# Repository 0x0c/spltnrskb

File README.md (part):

# nrsk 分割キーボード v2（基板と筐体）

KLE レイアウト（`kle/left.json`、`kle/right.json`）から生成した、左右分割・有線接続のキーボード基板です。
KiCad 10 のプロジェクト（回路図と配線済み基板）、製造用ガーバー、BOM、QMK ファームウェア設定を含みます。筐体のデータ（アクリルのレーザーカット用 DXF/SVG と 3D プリント用 STL）も入っています。

v2 では Pro Micro などのマイコンボードをやめ、RP2040 と QSPI Flash、USB-C コネクタなどを基板に直接実装しました。
マイコンボード用に設けていた内側の帯（約 20 mm）がなくなり、基板はキー領域とほぼ同じ大きさになっています。

| 項目 | 内容 |
| --- | --- |
| キー数 | 左 38 + 右 42 = 80 |
| マイコン | RP2040（QFN-56、12 MHz 水晶、I/O 3.3 V）と 16 MB の QSPI Flash W25Q128JV を左右に 1 組ずつ、裏面に直接実装 |
| USB | USB-C（USB 2.0）を左右それぞれに搭載 |
| 左右接続 | USB-C（片側にもう 1 つ、PC 用と同じレセプタクル）と USB-C ケーブル（C-C、データ通信用）。QMK の PIO シリアル（半二重、D+ の 1 本）と 5 V 給電 |
| スイッチ | Cherry MX 互換、Kailh MX ホットスワップソケット（裏面） |
| 基板 | 2 層、左 161.1 × 126.3 mm、右 180.5 × 126.3 mm（キー配列の外周から 3 mm を基本に、上端を 6 mm、内側を左 17.0 mm・右 12.6 mm 広げて OLED、USB-C 2 つ、マイコンの場所を確保）、四隅は半径 4 mm の角丸、M2 取付穴 × 8（片側あたり）、表裏とも GND のベタ（約 5 mm 間隔のビアで表裏をつなぐ） |
| 筐体 | 左 178.1 × 143.3 mm、右 197.5 × 143.3 mm、高さ 15.6 mm（3D プリント版）／ 16.5 mm（アクリル版）、いずれもプレート上面まで |
| 外観 | プレートは透明アクリル 1.5 mm、アクリル版の枠と底板はマットクリア 3 mm。プレートは外周の切り欠きなし。USB-C の 2 つの穴はコネクタの外形ぴったりで、高さも形も同じ（基板の舌でコネクタを壁の中まで出し、口は外面の約 1.3 mm 内側）。3D プリントのトレイは外周の角をフィレット加工（B のプレートも上面の外周に半径 1 mm の R） |
| 表示 | 0.91 インチ OLED（128×32）を左右に 1 枚ずつ、プレートと面一のハーフミラーアクリルのカバー付き。高さは増えない |
| ホイール | 左上と右上の角にサムホイール（ロータリーエンコーダー Alps EC05E1220401 で読み取り、1 回転 12 クリック）。高さは増えない |
| ドラム | 右半分の上段、F12 の右の空きに、手前と奥へ転がすドラム式ダイヤル（ロータリーエンコーダー Alps EC10E1220505 で読み取り、1 回転 24 クリック）。縦スクロールを送る。高さは増えない |
| 3D ビューア | http://www.0x0c.me/spltnrskb/ 、組み立てガイドは http://www.0x0c.me/spltnrskb/assembly.html 、写実的な 3D 表示は http://www.0x0c.me/spltnrskb/views.html 、エンコーダーの検証基板の 3D 表示は http://www.0x0c.me/spltnrskb/enctest-views.html （GitHub Pages、`main` への Push で自動更新） |

基板の表と裏です（KiCad の 3D 表示）。裏面は裏から見た向きなので、左右が反転して見えます。

| | 左 | 右 |
| --- | --- | --- |
| 表 |  |  |
| 裏 |  |  |

完成イメージ（Blender でレンダリング）です。筐体は 2 つの 3D プリント版を採用しています。左が A（3D プリントのトレイ + 透明アクリルのプレート）、右が B（プレートも 3D プリント）です。A はプレートを上から小ねじで、B は底からネジで留めます（B の上面にはネジが見えません）。

A と B は http://www.0x0c.me/spltnrskb/views.html で、3D のまま好きな角度から見られます。ドラッグで回転、ホイールかピンチで拡大します。「自動回転」をオンにすると、ゆっくり回り続けます（触っている間は止まり、手を離して 3 秒ほどで再開します）。形状、材質、照明は Blender のレンダリングと同じです。基板は、KiCad から書き出した実装済みのものです（`gen/export_3d.py` で `build/3d/` に作る）。「パストレース」をオンにすると、手を止めている間、ブラウザでパストレーシング（three-gpu-pathtracer）が進み、写真のような画が得られます。GPU を使い続けるので、最初はオフです。オンのときの自動回転は、選んだサンプル数まで描いてから 30° ずつ回ります。ボケとケーブル、台座（3°、6°、9°）も表示を切り替えられます。手元で開くときは `python3 -m http.server -d docs` で [docs/views.html](docs/views.html) を配信してください。ページの下には寄りの画像（打鍵する位置から、背面、側面、角、キーキャップ、ホイール、ドラム式ダイヤル、差込口。ケーブルを抜いた全体・背面・差込口も）が並び、クリックすると拡大します。台座に載せた姿も、側面と背面の 2 枚があります。3D 表示のモデル・照明・床の影は `gen/export_web3d.sh`（4 分ほど）で、寄りの画像は `gen/render_details.sh`（1 枚 3 分ほど）で作り直せます。

## 回路

各半分に同じ回路が載っています。Raspberry Pi の RP2040 設計ガイド（Hardware design with RP2040）の最小構成に、保護部品を加えた構成です。

| 機能 | 部品 |
| --- | --- |
| QSPI Flash | W25Q128JVS（16 MB、SOIC-8 208 mil）、0.1 µF |
| クロック | 12 MHz 水晶（3225）、15 pF × 2、XOUT に 1 kΩ 直列 |
| 電源 | VCC（5 V）→ LDO AP2112K-3.3（入出力 1 µF）→ 3V3。コアの 1.1 V は RP2040 内蔵レギュレータ（VREG_VIN／VREG_VOUT に 1 µF） |
| 電源のパスコン | IOVDD × 6、DVDD × 2、USB_VDD、ADC_AVDD にそれぞれ 0.1 µF、3V3 に 10 µF |
| USB | 27 Ω × 2（D+/D−）、CC 用 5.1 kΩ × 2（USB-C のデバイス認識用）、ESD 保護 USBLC6-2SC6 |
| 左右接続の USB-C | VBUS = VCC（5 V）、D+（A6、B6）= DATA、GND。D− と CC は未接続。DATA と VCC に ESD 保護 USBLC6-2SC6（PC 用の口と同じ部品） |
| 電源経路 | VBUS → ポリスイッチ 500 mA → ショットキーダイオード B5819W → VCC（5 V、左右接続の USB-C で反対側にも給電） |
| リセットと書き込み | RUN を 10 kΩ でプルアップしたリセットスイッチ（裏面）。BOOTSEL は QSPI_SS から 1 kΩ を通したはんだジャンパー |
| 左右判定 | GP0 を 10 kΩ で左は 3V3、右は GND に接続 |

- ショットキーダイオードは逆流を防ぎます。左右接続のケーブルで給電されている側でも、PC 用の USB-C の VBUS には電圧が出ないので、両方の USB を挿してもホスト側に電流が逆流しません。USB を挿していない側が自分をマスタだと誤判定することもありません。
- RP2040 はブートローダーを ROM に持っています。Flash が空のときは USB を挿すだけで `RPI-RP2` ドライブとして見え、UF2 ファイルをコピーすれば書き込めます。一度 QMK を書き込んだあとは、リセットスイッチを素早く 2 回押すと同じ書き込みモードに入ります。ISP 書き込み器は必要ありません。
- 左右接続の DATA は、通電したまま抜き差しするコネクタから RP2040 の GPIO へ直接つながります。そこで、コネクタのすぐ後ろに ESD 保護素子を置いています。直列抵抗は入れていません。QMK の半二重 PIO ドライバは、相手側が弱く High に駆動している線を Low に引く方式で、抵抗を入れると Low の電圧が上がるためです。
- OLED は 3.3 V で動かします。サムホイールとドラム式ダイヤルのエンコーダーは、A 相と B 相を RP2040 の内蔵プルアップで読み、共通端子を GND につないでいます。

### マルチプレクサは不要

片側のマトリックスは 6 行 × 8 列で、使う GPIO は 14 本です。
RP2040 の GPIO は 30 本あるので、シリアル通信 1 本、左右判定 1 本、I2C 2 本、エンコーダー 2 本を足しても十分に足ります。
列 7 を使うのは右の `\` キーだけで、左の列 7 は未接続です。QMK の分割キーボードは左右で同じ列数を前提とするため、左右とも 6 × 8 のマトリックスにそろえています。

### ピン割り当て（左右共通）

| 用途 | GPIO |
| --- | --- |
| ROW0〜ROW5 | GP4〜GP9 |
| COL0〜COL7 | GP10〜GP14、GP16〜GP18（GP15 は QFN の角で配線しにくいため使わない） |
| I2C1（OLED） | SDA = GP2、SCL = GP3 |
| サムホイールのエンコーダー | A 相 = GP19、B 相 = GP20（共通端子は GND） |
| ドラム式ダイヤルのエンコーダー（右だけ） | A 相 = GP22、B 相 = GP23（共通端子は GND） |
| 左右間データ | GP1、左右接続の USB-C の D+ |
| 左右判定 | GP0 |
| 予備 | GP15、GP21、GP24〜GP29（左は GP22、GP23 も） |

左右接続の USB-C は、VBUS に VCC（5 V）、D+ に DATA、GND をつなぎ、D− と CC は未接続です。D+ は表裏の 2 つのピン（A6、B6）をどちらも DATA につないでいるので、ケーブルはどちら向きに挿しても動きます。

- CC に抵抗（5.1 kΩ）を付けていないので、規格どおりの PC や充電器は、この口につながった相手を受電側と認識せず、VBUS に電圧を出しません。PC のケーブルを誤ってこの口に挿しても、何も起きません。
- 一方、この口の VBUS には、キーボードに電源が入っている間は VCC がそのまま出ています。キーボードを PC 用の口で PC につないだまま、この口を別の PC や充電器につながないでください。
- データ線のない充電専用のケーブルでは、左右が通信しません。データ通信に対応した USB 2.0 以上の C-C ケーブルを使ってください。

## 配置

- 表面: スイッチ、OLED、右半分のドラム式ダイヤルのエンコーダーです。スイッチプレートより上に出るのは、ドラム式ダイヤルの部品だけです（ベゼルで覆います）。
- 裏面: ホットスワップソケット、ダイオード、RP2040、Flash、LDO などの周辺部品、リセットスイッチ、BOOTSEL パッド、USB-C × 2、サムホイールのエンコーダー。
- 部品実装を頼む電子部品は、すべて裏面に載せています。JLCPCB の部品実装が片面で済み、両面より安くなります。部品の配置も、キーキャップや OLED のカバーを避ける制約がなくなり、単純になります。
- 2 つの USB-C はどちらも奥の辺（上端）に置き、ケーブルを後ろへ出します。左右接続用は内側の角寄り（OLED の上）、PC 用はその 18 mm 外側です。同じ部品なので、2 つの差込口の高さはそろいます。どちらも基板の外形を幅 12 mm の舌として壁の中まで伸ばし、舌の先端へコネクタを載せています。コネクタの口は舌の先端とそろえてあり、ケースの外面から約 1.3 mm 内側です（厚さ 0.8 mm の壁と、0.5 mm のすき間）。舌の先端の角は半径 2.5 mm、付け根は半径 0.8 mm の R を付けてあり、基板単体で持っても角が手に刺さりません。付け根の R は、筐体の壁とトンネルの角を避ける大きさです。
- 基板と筐体は、左右それぞれのキー配列にぴったり合わせた大きさです（左は OLED の分だけ内側を広げています）。
- 2 u 以上のキー（左 Shift 2.25 u、右 Backspace 2 u、右 Enter 2.25 u）には PCB マウント型スタビライザの穴があります。
- 配線幅は信号線 0.2 mm、電源線（GND、VCC）0.4 mm、USB の 5 V 入力（VBUS からヒューズ、ダイオードまで）0.3 mm です。クリアランスは 0.15 mm（GND のベタは 0.3 mm）、ビアは 0.6/0.3 mm です。最小配線幅は 0.15 mm で、RP2040 や USB-C の細いピンに入る短い区間だけで使っています。JLCPCB などの標準仕様（最小 0.127 mm）で製造できます。
- RP2040 の電源ピンのパスコンは、ほかの部品より先に、電源側のパッドをピンへ向けて置いています（ピンからパスコンのパッドまで、左 4.3〜5.1 mm、右 4.3〜6.8 mm）。GND のベタをつなぐビアは、半田付けするパッドとその周り 0.3 mm には打ちません（ビアの穴に半田が吸われるのを防ぐため）。
- 裏面のシルクには、基板名のほかに `RESET`（リセットスイッチ）と `BOOT`（BOOTSEL パッド）の表示があります。`JLCJLCJLCJLC` の文字は、JLCPCB が製造番号を入れる位置の指定です。
- ホットスワップソケットのパッドには、ペースト層を出していません。ソケットは実装のあとに手で半田付けします。先に半田が盛られていると、ソケットが浮くためです。
- マイコン周りの部品番号はシルクに収まらないため、Fab 層に入れています。半田付けには `fab/<side>/nrsk-<side>-assembly-back.pdf`（裏面の実装図、左右反転済み）を使ってください。配線の確認には `fab/<side>/nrsk-<side>-copper.pdf` を使えます（1 ページ目が表面 F.Cu、2 ページ目が裏面 B.Cu で、どちらも外形付き）。

## サムホイール（角のダイヤル）

左半分の左上、右半分の右上の角に、親指でなぞって回すサムホイールを付けています。

- 形: 直径 29.2 mm、厚さ 4.1 mm のホイールで、外周に 32 山の丸い歯（深さ 0.5 mm）があります。歯は指のすべり止めです。角の丸みと同心に置いていて、縁が角から約 3.5 mm、両側面から約 1 mm 出ます。
- 位置: 基板と底のすき間（7 mm）に水平に寝かせています。壁の下側だけを切り欠くので、プレートと壁の上部は切れ目がありません。キーボードの高さも変わりません。
- 検出: 基板裏面のホイールの中心の真上に、中空シャフトのロータリーエンコーダー Alps EC05E1220401 を下向きに付けています。ホイール上面の六角ピン（対辺 1.66 mm）が、エンコーダーの六角穴（対辺 1.72 mm）に 2 mm 入って回転部を回します。エンコーダーの下面に当たらないよう、ホイール上面の中心（半径 6 mm）を 0.4 mm 下げています。基板には、回転部の下に 3 mm 角の穴があります。
- クリック: エンコーダーが内蔵するクリックを使い、1 回転 12 クリック（30° ごと）です。1 クリックで A 相と B 相がちょうど 1 周期進むので、クリックとファームウェアの 1 ステップは部品の中で一致しています。
- 軸: 3D プリント版はトレイの床から立てた軸（直径 3.6 mm）、アクリル版は底板の下から通す M3 ネジを軸にします。ホイールの下面には軸穴（直径 4 mm × 深さ 2 mm）があります。親指で押す横向きの力はこの軸で受け、エンコーダーには回転だけを伝えます。軸と軸穴の間に半径方向で 0.2 mm 以上のすき間を設けて、基板とケースの位置ずれでホイールがこじれないようにしています。
- 組み立て: 3D プリント版で基板をトンネルへ滑り込ませるとき、エンコーダーの下面は六角ピンの先端の約 0.3 mm 上を通ります。ホイールのある角を少し持ち上げて滑らせてください。基板を下ろすときは、ホイールの縁を指で少し回すと、ピンがエンコーダーの穴に入ります。
- 左の Esc キー: エンコーダーと Esc のホットスワップソケットが重ならないよう、基板の上端を 1 mm 余分に延ばしてホイールを上へずらしています。そのため、すべてのスイッチを同じ向きで取り付けます。
- ファームウェア: QMK のエンコーダー機能で読みます。エンコーダーは基板の裏で下を向いているので、A 相と B 相のピンを入れ替えて設定し、上から見た時計回りを正の向きとして扱います。USB をつないでいない側のホイールも、QMK が左右間の通信で送ります。

| | 左ホイール | 右ホイール |
| --- | --- | --- |
| 回す（レイヤー 0） | 音量 | ページ上下 |
| 回す（レイヤー 1） | 画面の明るさ | カーソル左右 |

割り当ては `keymap.c` の `encoder_update_user()` で変更できます。

検討段階の記録として、側面ダイヤルの 2 タイプ（サムホイール型と横向きノブ型）を比べたレンダリングは [docs/img/dial-study/dial-grid.jpg](docs/img/dial-study/dial-grid.jpg) にあります。サムホイール型を採用し、角に置きました。

読み取りの方式は、当初の磁気角度センサー AS5600 と磁石、ボールプランジャーの組み合わせから、市販のロータリーエンコーダーに変えました。理由と検討した代替案は [docs/specs/thumbwheel-encoder.md](docs/specs/thumbwheel-encoder.md) に、両者の断面の比較は [docs/img/encoder-study/sheet.jpg](docs/img/encoder-study/sheet.jpg) にあります。

## ドラム式ダイヤル（右上）

右半分の上段で、F12 の右に空いている 2 u の場所に、手前と奥へ転がすドラム式のダイヤルを付けています。奥へ転がすと上へ、手前へ転がすと下へスクロールします（レイヤー 1 では左右へスクロール）。

- 形: 直径 13 mm、幅 21.6 mm のドラムで、表面に斜めのローレット（ねじれ角 30°、溝 36 本、深さ 0.4 mm）があります。細かいローレットを出すため、光造形の樹脂で作ります（`case/print/right-drum.stl`）。
- 高さ: 軸は基板の上面から 7 mm です。ドラムの上端はプレートから 8.5 mm 出て、キーキャップの上面より 4.5 mm 低くなります。キーボードの高さは変わりません。
- 位置: ドラムを囲むベゼルは、左右のフードが同じ大きさの対称な形で、2 u の空きをほぼ埋めています。左は F12 との間のプレートの帯、右は筐体の壁で端が決まるので、ベゼルとドラムの中心は下の段の Backspace（2 u）の中心より約 0.7 mm 右に来ます。
- 検出: 軸が基板と平行な横型のロータリーエンコーダー Alps EC10E1220505（1 回転 24 クリック、12 パルス）を、ドラムの左に表面から差し込みます。ドラムの左端の六角ピン（対辺 1.66 mm）が、エンコーダーの六角穴（対辺 1.73 mm）に 1.6 mm 入って回します。ピンは根元から先まで対辺 1.66 mm の六角のままで、先端の縁だけを 0.2 mm 面取りしています。
- 軸受け: ドラムの右端の丸ピン（直径 2 mm）を、基板の穴 2 つに差し込んだ 3D プリントの軸受けブロックが受けます。ブロックの位置決めピンは基板の下へ出ないので、基板の下のサムホイールとは当たりません。ブロックの溝は上が開いた U 字で、入口を 1.8 mm に絞ってあるので、ピンを上から押し込むとはまって抜けません。指で押し下げる力は、エンコーダーとブロックの両方で受けます。
- ベゼル: 3D プリントのベゼル（`case/print/right-drum-bezel.stl`）の枠を、プレートの穴に収めます。枠の上面はプレートと面一で、段差はありません。プレートを載せる前にベゼルを基板の上に置き、上からプレートをかぶせます。枠の下のつばがプレートの下面に当たってベゼルが抜けるのを止め、軸受けブロックの上面とエンコーダー側の脚が下から支えます。ベゼルのフードがエンコーダーを覆い、もう一方のフードの天井が軸受けブロックを押さえます。A、B、アクリル版で同じ部品を使います。
- ファームウェア: QMK のエンコーダー機能で読みます（右半分の 2 個目のエンコーダー）。1 クリックで A 相と B 相が半周期だけ進むので、分解能（`resolution`）を 2 にしています。マウスのホイールのキーコードを送るため、QMK のマウスキー機能を有効にしています。実機で向きが逆なら、`gen/make_qmk.py` の `pin_a` と `pin_b` を入れ替えます。

設計の経緯と、検討した代替案は [docs/specs/drum-dial.md](docs/specs/drum-dial.md) にあります。

## OLED

左右に 0.91 インチの OLED モジュール（128×32、SSD1306、I2C）を 1 枚ずつ付けています。

- 配線: RP2040 の GP3（SCL）と GP2（SDA）に接続し、4.7 kΩ でプルアップしています。モジュールのピン順は GND / VCC / SCL / SDA です。VCC と GND が逆のモジュールもあるので、購入前に確認してください。
- 配置: 左右とも内側の端、1〜2 段目の高さに縦向きで置き、上端からの位置をそろえています。モジュールは左右とも同じ向き（ピンヘッダが下）なので、ファームウェアの表示の向きは 1 つで済みます。右は 3 段目のキーの上の切り欠きに収まり、左は基板の内側を広げて、カバーの周りに 5.5 mm の帯を取っています（次の「筐体」）。
- 取り付け: ピンヘッダの黒い樹脂スペーサーを外し、OLED のガラス上面が基板の上面から 2.5 mm の高さになるように、モジュールを基板に近づけて半田付けします。
- 筐体: ハーフミラーのアクリルのカバー（`case/laser/<side>-oled-cover`）を、プレートの切り欠きにはめ込みます。カバーの周りに残るプレートの帯は、筐体の外周（上辺と内側の辺）までも、横のキーキャップまでも 5.5 mm です。カバーの 4 つの角はすべて R7 です。筐体の角に面する角は筐体の角（R12.5）と同心なので、帯の幅は角でも変わりません。帯の近くの外周のネジは省いています。カバーの下端は OLED モジュールの端から 1.5 mm 下で、OLED の表示（ガラス）がカバーの中央に来るように置いています。そのため、右のカバーの下の Y キーとの帯だけは 2.7 mm です。ハーフミラーのアクリルは 2 mm 厚からしか市販されていません。そこで 3D プリント版は壁の上面をカバーの下だけ 0.5 mm 下げて、上面をプレートと面一にしています（アクリル版は 0.5 mm 高くなります）。カバーは OLED のガラス面と壁の上面に透明両面テープで貼り、ネジは使いません。消灯中は鏡のように見え、点灯すると表示が透けて見えます。カバーの周りに余白を取るため、基板の上端を 5 mm 延ばし（ホイールのためにさらに 1 mm 延ばして計 6 mm）、内側を広げています。
- 表示: QMK の `oled_task_user` で、USB をつないだ側にレイヤーと Caps Lock、もう一方に WPM を表示します。処理は `firmware/qmk/keyboards/nrsk/keymaps/default/keymap.c` にあります。

### OLED の高さ・角度の比較

検討段階の記録です（採用したのは、上に書いたプレートと面一のハーフミラーのカバーです）。画像は今の基板・筐体の形で描き直しています。台座の位置は外形から計算し、壁の上に収まるように置いています。
キーキャップに隠れにくい OLED の付け方を、高さ 0〜13 mm の 4 案（A〜D）と傾斜 2 案（E・F）で比べました。
座った目線と寄りのレンダリングを、取り付け方式ごとに [docs/img/render-grid.jpg](docs/img/render-grid.jpg) にまとめています。
台座の形状は `gen/oled_variants.py`、レンダリングは `gen/render_all.sh` で作り直せます。デフォルトは確認用のプレビュー（長辺 1200 px、数分）で、`FINAL=1 ./gen/render_all.sh` とすると高画質（長辺 2400 px）で出力します。
B〜F は OLED を基板の外側（壁の上）へ移すため、基板のコネクタから配線でつなぐ前提です。

## 筐体

3D プリントとアクリルのレーザーカットのどちらでも作れるよう、同じ寸法のサンドイッチ構造にしています。3D プリントのトレイを使う版は 2 種類あり、どちらも正式な仕様です。

- **A：トレイ + 透明アクリルのプレート** — トレイは 3D プリント、スイッチプレートは透明アクリル 1.5 mm（`case/laser/<side>-plate`）。プレート越しに基板が見えます。
- **B：全部 3D プリント** — プレートも 3D プリント（`case/print/<side>-plate.stl`）。スイッチの爪が掛かる周りだけ 1.5 mm で、ほかは裏に 2 mm の補強があり、上下を逆にして印刷します。中は見えません。
- **アクリル版** — 底板・枠・プレートをすべてアクリルのレーザーカットで積み重ねます。

トレイは A と B で共通です。壁の中を縦にネジ穴が通り、上面には丸いくぼみ、底には座ぐり（φ4.6 × 1.6 mm）があります。A は透明アクリルのプレートを、上から通したなべ小ねじ M2 × 16 mm と、底の座ぐりに押し込んだ M2 ナットで留めます。くぼみの下には六角のナット受けもありますが、使いません。ナット受けは上に開いているので、上から締めるネジではナットが引き上げられるだけで、プレートを締め付けられないためです。B は、プレート裏のボスに入れたヒートセットインサートへ、トレイの底の座ぐりから M2 × 12 mm のなべネジで留めるので、上面にネジは見えません。アクリル版は上から M2 × 20 mm で底板の下のナットまで共締めします。
基板は 8 か所の取り付け穴で筐体の底に固定し、スイッチプレートは外周のネジで留めます。
寸法の基準は MX の規格（プレート上面から基板上面まで 5.0 mm）です。

| 部分 | A / B（3D プリントのトレイ、`case/print/`） | アクリル版（`case/laser/`） |
| --- | --- | --- |
| 底 | トレイの床 2 mm、外周の下端 R2・上端 R0.6 のフィレット | 底板 3 mm（`<side>-bottom`） |
| 壁 | トレイと一体、幅 8 mm、高さ 14.1 mm。ホイールの上は外せる角キャップ（`<side>-wheel-cap.stl`）。キャップの下段から出た 2 つの爪（奥の壁と側面の壁に 1 つずつ）がトレイの溝に入るので、キャップは回りません | 枠 3 mm × 4 枚（差込口のある枠には切り欠き、`frame4` は切り欠きなし） |
| 基板の支持 | 床から高さ 7 mm のボス（φ4.6、下穴 φ1.6）に M2 × 6 mm タッピングネジ | M2 × 7 mm スペーサーに、上から M2 × 4 mm、下から M2 × 5 mm のネジ |
| プレート | A：透明アクリル 1.5 mm、上から M2 × 16 mm のなべ小ねじで底の座ぐりのナットへ／B：3D プリント（補強付き、裏のボスに M2 インサート）、底の座ぐりから M2 × 12 mm | 透明アクリル 1.5 mm、上から M2 × 20 mm とナットで底板まで共締め |
| ネジ本数 | 外周 左右 10 ずつ、基板 左右 8 ずつ | 同じ |

設計上の注意点です。

- 取り付け穴は、スペーサーやボスが裏面のパッドや配線に触れない位置へ置きました（穴の中心から銅箔まで 2.75 mm 以上）。穴の周りには配線禁止の領域を設けています。
- 2 つの USB-C は、基板の舌に載せて壁の中まで出しています。壁の外面にはコネクタの外形に 0.2 mm を足した角丸の長穴だけが開き、プラグの根元はすべてケースの外に出るので、ほとんどのケーブルが使えます。アクリル版は、舌とコネクタの高さの枠 2 枚（`frame2`、`frame3`）を、2 つの差込口をまたぐ 1 つの切り欠きで開けています。アクリルでは差込口の前に 0.8 mm の壁を残せず、差込口ごとに切ると間に固定できない小片が残るためです。プレートと最上段の枠は切れ目のない輪のままです。

- 3D プリント版のトレイは、差込口のまわりも分割しない一体の部品です。舌とコネクタは、奥の壁の中の上が閉じたトンネルに収まります。トンネルの高さは、舌の上に 2.3 mm の余裕があります。この余裕の分だけ基板を浮かせれば、裏面の部品がボスの上を通り抜けられます（実装済みの基板の 3D モデルで確かめた最小値は 1.5 mm）。トンネルの上には厚さ 1.2 mm の天井が残ります（OLED カバーの下のくぼみに掛かる、左右接続用の USB-C 側の一部は 0.7 mm）。
- 基板は、手前の縁を約 2° 持ち上げて手前の壁の上端を越えさせ、ボスより 2 mm 浮かせて奥の壁に近づけます。舌を 2 つのトンネルに差し込みながら奥へ 8 mm 滑らせ、手前を下ろしてボスに載せます。下の図は、左の USB-C の中心を通る断面で、左側がケース全体、右側が差込口まわりの拡大です。

- 基板を床から 7 mm 浮かせているのは、ホイールとエンコーダー、裏面の部品のためです。
- 底面には、リセットスイッチをピンで押すための φ3 mm の穴があります。
- トレイの幅は左 178.1 mm、右 197.5 mm です。どちらも 220 mm 角の造形範囲（Ender-3、Bambu Lab A1/P1/X1、Prusa MK4 など）に入ります。180 mm 角の機種（A1 mini など）では入りません。
- B のプレートは PETG など粘りのある材料が向いています。A のプレートと同じ DXF から、アクリルのほか FR4 1.6 mm やアルミ 1.5 mm で外注できます。
- アクリル版の枠 4 枚の合計は 12.0 mm です。設計上の理想値 12.1 mm より 0.1 mm 薄く、その分プレートがスイッチを押し下げますが、アクリル板自体の厚み公差（±0.2 mm 程度）の範囲内です。気になる場合は、スペーサーの下に薄いワッシャーを挟んでください。
- レーザーカット用のプレート（`case/laser/<side>-plate`）は、スイッチ穴の角に半径 0.3 mm の R を付けています。スタビライザーの穴とスイッチ穴の間の桟（幅 1.4 mm）はなくして、1 つの穴にしています。細い桟は切り出せず、鋭い角はアクリルの割れの起点になるためです。`make_case.py` は、切り出す部品に幅 1 mm 未満の部分がないことを確かめます。離れた部品がどれも 2 本以上のネジで留まることも確かめ、幅 3 mm 未満の箇所を一覧で表示します。
- レーザーカットを外注するときは、DXF（単位 mm、全線カット）をそのまま入稿できます。スイッチ穴 14.0 mm はカット幅の補正が前提なので、補正の有無を業者に確認してください。

`case/preview/viewer.html` は組み立て状態を回して見られる 3D ビューアです。http://www.0x0c.me/spltnrskb/ で公開しています（`.github/workflows/pages.yml`）。
基板は KiCad の 3D プレビューと同じ部品実装済みの姿で表示します（`gen/export_3d.py` で KiCad から書き出し、`gen/glb_mesh.py` でブラウザ向けに軽量化）。
「分解表示」をオンにすると、スライダーでレイヤーどうしの間隔を 0〜40 mm で変えられます。
「台座」で角度（なし、3°、6°、9°）を選ぶと、台座に載せて傾けた姿になります。ケース、プレート、基板、スイッチ、ダイヤル、ゴム足、台座は、チェックボックスでそれぞれ表示と非表示を切り替えられます。

組み立て手順は、同じデータを使ったインタラクティブな組み立てガイド（`case/preview/assembly.html`、公開版は [http://www.0x0c.me/spltnrskb/assembly.html](http://www.0x0c.me/spltnrskb/assembly.html)）で確認できます。手順ごとに部品が所定の位置に入るアニメーションと説明が出て、A・B・アクリル版と左右を切り替えられます。

### Fusion の設計と、基板を変えたときの更新

3D プリントの部品の形は、Autodesk Fusion の設計 `nrsk-left-case` と `nrsk-right-case`（Hybrid Design）が正です。対象はトレイ、B のプレート、ホイール、ホイールのキャップ、台座、ドラム式ダイヤル一式です。形を変えるときは、Fusion の GUI で編集します。リポジトリには、節目ごとに書き出した設計（`case/fusion/nrsk-<side>-case.f3d`）と部品ごとの STL（`case/fusion/<side>/`）を置いています。`gen/make_case.py` はその STL を読み込み、干渉チェックをしてから `case/print/` と `case/preview/` へ書き出します。アクリル版と、検証基板のトレイとプレートは、従来どおり `make_case.py` が作ります。

寸法の定数の正は `make_case.py` です。Fusion のユーザーパラメータは同じ名前で、同期のたびに `make_case.py` の値で上書きされます。Fusion で値を変えて決めたら、`make_case.py` にも書き戻してください。

Fusion のスクリプトは `fusion/` にあります。`fusion/link.sh` を 1 度実行すると、Fusion の「ユーティリティ」タブの「アドイン」から開く「スクリプトとアドイン」の一覧に載ります。

- `NrskCaseSync`：基板から来る寸法を Fusion の設計に反映します。
- `NrskCaseExport`：部品ごとの STL と `.f3d` を `case/fusion/` に書き出します。
- `NrskCaseLayout`：Fusion の画面で、各部品を組み立てた位置に表示します（台座は 3° だけ）。部品は書き出す座標系で作ってあるので、そのままではホイールが床に、プレートがトレイにめり込んで見えます。配置を動かすだけなので、書き出す STL は変わりません。
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
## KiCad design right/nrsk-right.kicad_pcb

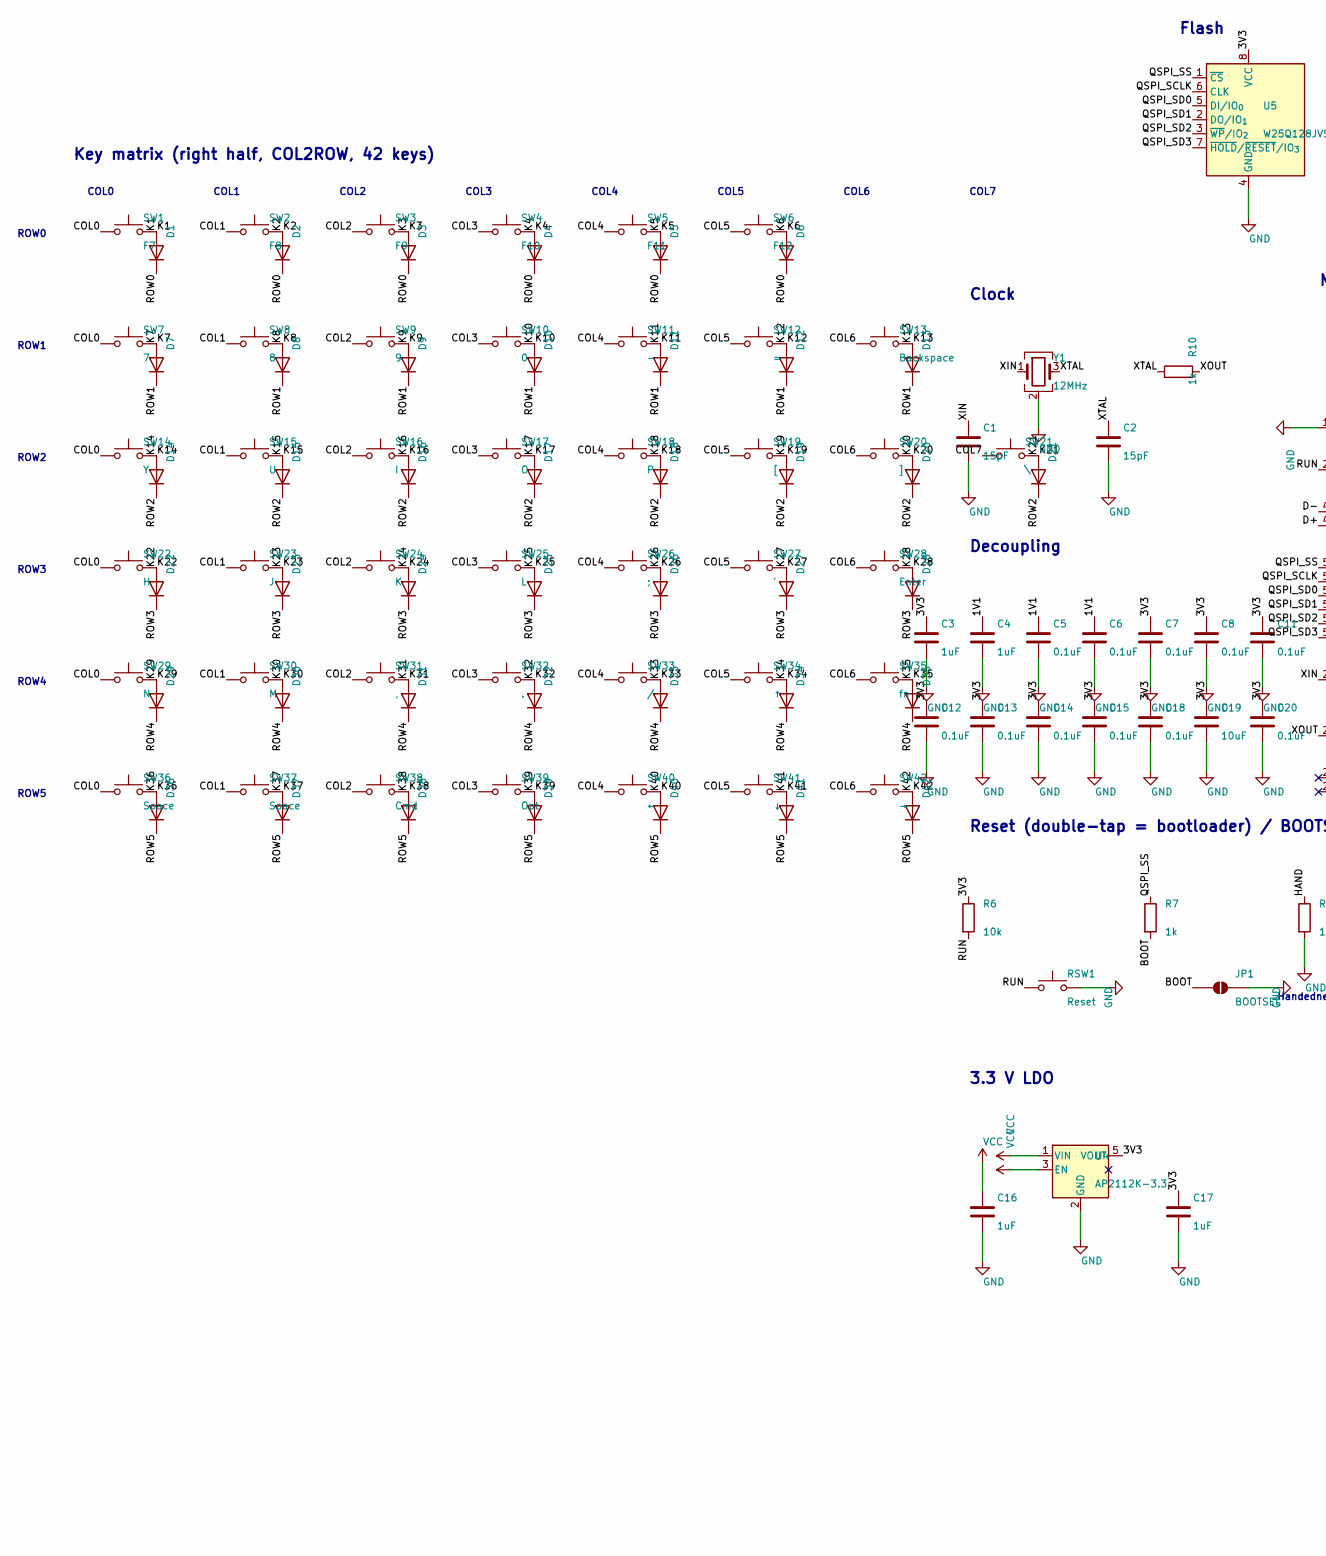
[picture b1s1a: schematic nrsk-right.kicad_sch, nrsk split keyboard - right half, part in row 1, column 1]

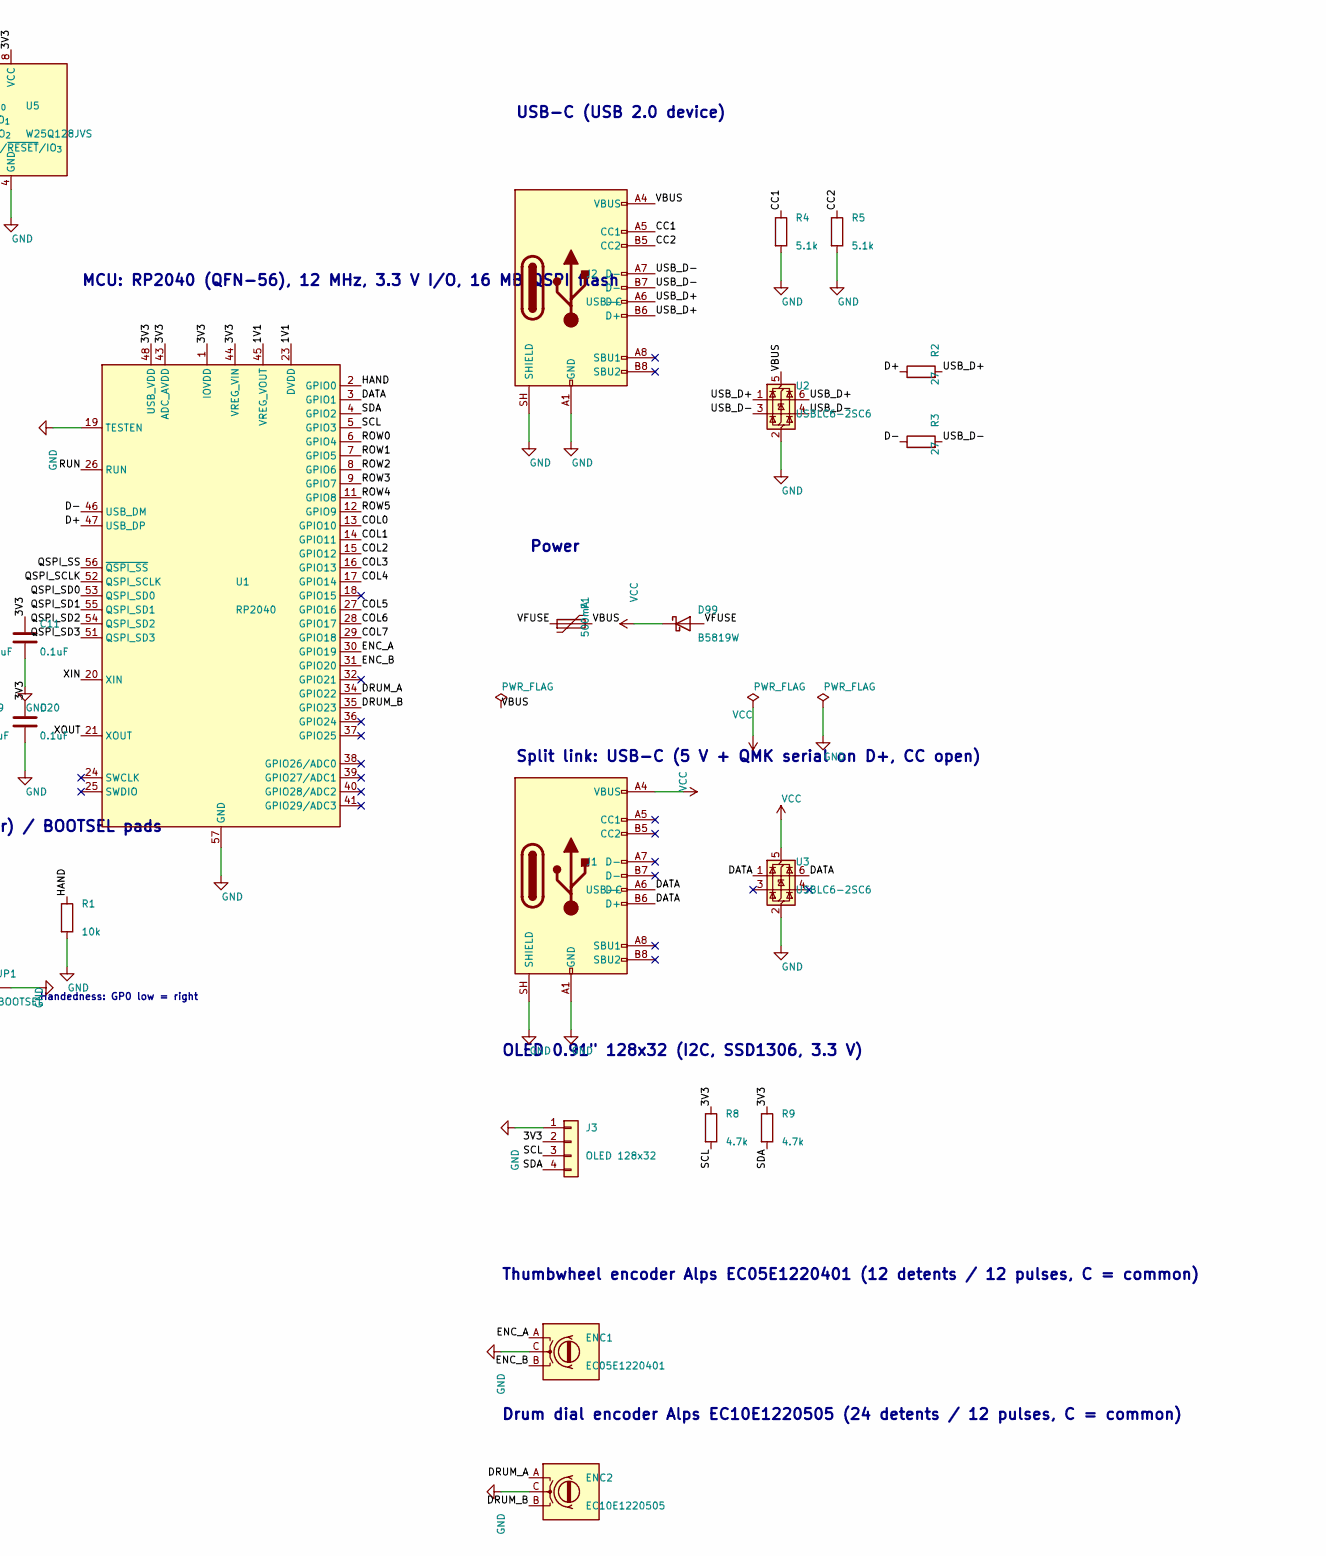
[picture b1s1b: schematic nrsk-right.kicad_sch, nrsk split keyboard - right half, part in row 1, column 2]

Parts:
C1, C2: 15pF; C_0805_2012Metric
C3, C4, C16, C17: 1uF; C_0805_2012Metric
C5, C6, C7, C8, C11, C12, C13, C14, C15, C18, C20: 0.1uF; C_0805_2012Metric
C19: 10uF; C_0805_2012Metric
D1, D2, D3, D4, D5, D6, D7, D8, D9, D10, D11, D12, D13, D14, D15, D16, D17, D18, D19, D20, D21, D22, D23, D24, D25, D26, D27, D28, D29, D30, D31, D32, D33, D34, D35, D36, D37, D38, D39, D40, D41, D42: 1N4148W; D_SOD-123
D99: B5819W; D_SOD-123
ENC1: EC05E1220401; Alps_EC05E1220401
ENC2: EC10E1220505; Alps_EC10E
F1: 500mA; Fuse_1206_3216Metric
J1, J2: USB-C; USB_C_Receptacle_HRO_TYPE-C-31-M-12
J3: OLED 128x32; OLED_0.91in_128x32_I2C
JP1: BOOTSEL; SolderJumper-2_P1.3mm_Open_RoundedPad1.0x1.5mm
R1, R6: 10k; R_0805_2012Metric
R2, R3: 27; R_0805_2012Metric
R4, R5: 5.1k; R_0805_2012Metric
R7, R10: 1k; R_0805_2012Metric
R8, R9: 4.7k; R_0805_2012Metric
RSW1: Reset; SW_SPST_PTS810
SW1: F7; SW_MX_Hotswap_1.00u
SW2: F8; SW_MX_Hotswap_1.00u
SW3: F9; SW_MX_Hotswap_1.00u
SW4: F10; SW_MX_Hotswap_1.00u
SW5: F11; SW_MX_Hotswap_1.00u
SW6: F12; SW_MX_Hotswap_1.00u
SW7: 7; SW_MX_Hotswap_1.00u
SW8: 8; SW_MX_Hotswap_1.00u
SW9: 9; SW_MX_Hotswap_1.00u
SW10: 0; SW_MX_Hotswap_1.00u
SW11: -; SW_MX_Hotswap_1.00u
SW12: =; SW_MX_Hotswap_1.00u
SW13: Backspace; SW_MX_Hotswap_2.00u
SW14: Y; SW_MX_Hotswap_1.00u
SW15: U; SW_MX_Hotswap_1.00u
SW16: I; SW_MX_Hotswap_1.00u
SW17: O; SW_MX_Hotswap_1.00u
SW18: P; SW_MX_Hotswap_1.00u
SW19: [; SW_MX_Hotswap_1.00u
SW20: ]; SW_MX_Hotswap_1.00u
SW21: \; SW_MX_Hotswap_1.50u
SW22: H; SW_MX_Hotswap_1.00u
SW23: J; SW_MX_Hotswap_1.00u
SW24: K; SW_MX_Hotswap_1.00u
SW25: L; SW_MX_Hotswap_1.00u
SW26: ;; SW_MX_Hotswap_1.00u
SW27: '; SW_MX_Hotswap_1.00u
SW28: Enter; SW_MX_Hotswap_2.25u
SW29: N; SW_MX_Hotswap_1.00u
SW30: M; SW_MX_Hotswap_1.00u
SW31: ,; SW_MX_Hotswap_1.00u
SW32: .; SW_MX_Hotswap_1.00u
SW33: /; SW_MX_Hotswap_1.00u
SW34: ↑; SW_MX_Hotswap_1.00u
SW35: fn; SW_MX_Hotswap_1.00u
SW36, SW37: Space; SW_MX_Hotswap_1.00u
SW38: Cmd; SW_MX_Hotswap_1.25u
SW39: Opt; SW_MX_Hotswap_1.25u
SW40: ←; SW_MX_Hotswap_1.00u
SW41: ↓; SW_MX_Hotswap_1.00u
SW42: →; SW_MX_Hotswap_1.00u
U1: RP2040; QFN-56-1EP_7x7mm_P0.4mm_EP3.2x3.2mm
U2, U3: USBLC6-2SC6; SOT-23-6
U4: AP2112K-3.3; SOT-23-5
U5: W25Q128JVS; SOIC-8_5.3x5.3mm_P1.27mm
Y1: 12MHz; Crystal_SMD_3225-4Pin_3.2x2.5mm

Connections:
/1V1: C4.1, C5.1, C6.1, U1.23 (DVDD), U1.45 (VREG_VOUT), U1.50 (DVDD)
/3V3: C3.1, C7.1, C8.1, C11.1, C12.1, C13.1, C14.1, C15.1, C17.1, C18.1, C19.1, C20.1, J3.2, R6.1, R8.1, R9.1, U1.1 (IOVDD), U1.10 (IOVDD), U1.22 (IOVDD), U1.33 (IOVDD), U1.42 (IOVDD), U1.43 (ADC_AVDD), U1.44 (VREG_VIN), U1.48 (USB_VDD), U1.49 (IOVDD), U4.5 (VOUT), U5.8 (VCC)
/BOOT: JP1.1 (A), R7.2
/CC1: J2.A5 (CC1), R4.1
/CC2: J2.B5 (CC2), R5.1
/COL0: SW1.1, SW7.1, SW14.1, SW22.1, SW29.1, SW36.1, U1.13 (GPIO10)
/COL1: SW2.1, SW8.1, SW15.1, SW23.1, SW30.1, SW37.1, U1.14 (GPIO11)
/COL2: SW3.1, SW9.1, SW16.1, SW24.1, SW31.1, SW38.1, U1.15 (GPIO12)
/COL3: SW4.1, SW10.1, SW17.1, SW25.1, SW32.1, SW39.1, U1.16 (GPIO13)
/COL4: SW5.1, SW11.1, SW18.1, SW26.1, SW33.1, SW40.1, U1.17 (GPIO14)
/COL5: SW6.1, SW12.1, SW19.1, SW27.1, SW34.1, SW41.1, U1.27 (GPIO16)
/COL6: SW13.1, SW20.1, SW28.1, SW35.1, SW42.1, U1.28 (GPIO17)
/COL7: SW21.1, U1.29 (GPIO18)
/D+: R2.1, U1.47 (USB_DP)
/D-: R3.1, U1.46 (USB_DM)
/DATA: J1.A6 (D+), J1.B6 (D+), U1.3 (GPIO1), U3.1 (I/O1), U3.6 (I/O1)
/DRUM_A: ENC2.A, U1.34 (GPIO22)
/DRUM_B: ENC2.B, U1.35 (GPIO23)
/ENC_A: ENC1.A, U1.30 (GPIO19)
/ENC_B: ENC1.B, U1.31 (GPIO20)
/HAND: R1.1, U1.2 (GPIO0)
/K1: D1.2 (A), SW1.2
/K2: D2.2 (A), SW2.2
/K3: D3.2 (A), SW3.2
/K4: D4.2 (A), SW4.2
/K5: D5.2 (A), SW5.2
/K6: D6.2 (A), SW6.2
/K7: D7.2 (A), SW7.2
/K8: D8.2 (A), SW8.2
/K9: D9.2 (A), SW9.2
/K10: D10.2 (A), SW10.2
/K11: D11.2 (A), SW11.2
/K12: D12.2 (A), SW12.2
/K13: D13.2 (A), SW13.2
/K14: D14.2 (A), SW14.2
/K15: D15.2 (A), SW15.2
/K16: D16.2 (A), SW16.2
/K17: D17.2 (A), SW17.2
/K18: D18.2 (A), SW18.2
/K19: D19.2 (A), SW19.2
/K20: D20.2 (A), SW20.2
/K21: D21.2 (A), SW21.2
/K22: D22.2 (A), SW22.2
/K23: D23.2 (A), SW23.2
/K24: D24.2 (A), SW24.2
/K25: D25.2 (A), SW25.2
/K26: D26.2 (A), SW26.2
/K27: D27.2 (A), SW27.2
/K28: D28.2 (A), SW28.2
/K29: D29.2 (A), SW29.2
/K30: D30.2 (A), SW30.2
/K31: D31.2 (A), SW31.2
/K32: D32.2 (A), SW32.2
/K33: D33.2 (A), SW33.2
/K34: D34.2 (A), SW34.2
/K35: D35.2 (A), SW35.2
/K36: D36.2 (A), SW36.2
/K37: D37.2 (A), SW37.2
/K38: D38.2 (A), SW38.2
/K39: D39.2 (A), SW39.2
/K40: D40.2 (A), SW40.2
/K41: D41.2 (A), SW41.2
/K42: D42.2 (A), SW42.2
/QSPI_SCLK: U1.52 (QSPI_SCLK), U5.6 (CLK)
/QSPI_SD0: U1.53 (QSPI_SD0), U5.5 (DI/IO_{0})
/QSPI_SD1: U1.55 (QSPI_SD1), U5.2 (DO/IO_{1})
/QSPI_SD2: U1.54 (QSPI_SD2), U5.3 (~WP/IO_{2})
/QSPI_SD3: U1.51 (QSPI_SD3), U5.7 (~HOLD/~RESET/IO_{3})
/QSPI_SS: R7.1, U1.56 (~QSPI_SS), U5.1 (~CS)
/ROW0: D1.1 (K), D2.1 (K), D3.1 (K), D4.1 (K), D5.1 (K), D6.1 (K), U1.6 (GPIO4)
/ROW1: D7.1 (K), D8.1 (K), D9.1 (K), D10.1 (K), D11.1 (K), D12.1 (K), D13.1 (K), U1.7 (GPIO5)
/ROW2: D14.1 (K), D15.1 (K), D16.1 (K), D17.1 (K), D18.1 (K), D19.1 (K), D20.1 (K), D21.1 (K), U1.8 (GPIO6)
/ROW3: D22.1 (K), D23.1 (K), D24.1 (K), D25.1 (K), D26.1 (K), D27.1 (K), D28.1 (K), U1.9 (GPIO7)
/ROW4: D29.1 (K), D30.1 (K), D31.1 (K), D32.1 (K), D33.1 (K), D34.1 (K), D35.1 (K), U1.11 (GPIO8)
/ROW5: D36.1 (K), D37.1 (K), D38.1 (K), D39.1 (K), D40.1 (K), D41.1 (K), D42.1 (K), U1.12 (GPIO9)
/RUN: R6.2, RSW1.1, U1.26 (RUN)
/SCL: J3.3, R8.2, U1.5 (GPIO3)
/SDA: J3.4, R9.2, U1.4 (GPIO2)
/USB_D+: J2.A6 (D+), J2.B6 (D+), R2.2, U2.1 (I/O1), U2.6 (I/O1)
/USB_D-: J2.A7 (D-), J2.B7 (D-), R3.2, U2.3 (I/O2), U2.4 (I/O2)
/VBUS: F1.2, J2.A4 (VBUS), J2.A9 (VBUS), J2.B4 (VBUS), J2.B9 (VBUS), U2.5 (VBUS)
/VFUSE: D99.2 (A), F1.1
/XIN: C1.1, U1.20 (XIN), Y1.1
/XOUT: R10.2, U1.21 (XOUT)
/XTAL: C2.1, R10.1, Y1.3
GND: C1.2, C2.2, C3.2, C4.2, C5.2, C6.2, C7.2, C8.2, C11.2, C12.2, C13.2, C14.2, C15.2, C16.2, C17.2, C18.2, C19.2, C20.2, ENC1.C, ENC2.C, J1.A1 (GND), J1.A12 (GND), J1.B1 (GND), J1.B12 (GND), J1.SH (SHIELD), J2.A1 (GND), J2.A12 (GND), J2.B1 (GND), J2.B12 (GND), J2.SH (SHIELD), J3.1, JP1.2 (B), R1.2, R4.2, R5.2, RSW1.2, U1.19 (TESTEN), U1.57 (GND), U2.2 (GND), U3.2 (GND), U4.2 (GND), U5.4 (GND), Y1.2 (G), Y1.4 (G)
VCC: C16.1, D99.1 (K), J1.A4 (VBUS), J1.A9 (VBUS), J1.B4 (VBUS), J1.B9 (VBUS), U3.5 (VBUS), U4.1 (VIN), U4.3 (EN)

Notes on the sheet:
Key matrix (right half, COL2ROW, 42 keys)
COL0
COL1
COL2
COL3
COL4
COL5
COL6
COL7
ROW0
ROW1
ROW2
ROW3
ROW4
ROW5
MCU: RP2040 (QFN-56), 12 MHz, 3.3 V I/O, 16 MB QSPI flash
Flash
Clock
Decoupling
Reset (double-tap = bootloader) / BOOTSEL pads
Handedness: GP0 low = right
3.3 V LDO
USB-C (USB 2.0 device)
Power
Split link: USB-C (5 V + QMK serial on D+, CC open)
OLED 0.91" 128x32 (I2C, SSD1306, 3.3 V)
Thumbwheel encoder Alps EC05E1220401 (12 detents / 12 pulses, C = common)
Drum dial encoder Alps EC10E1220505 (24 detents / 12 pulses, C = common)

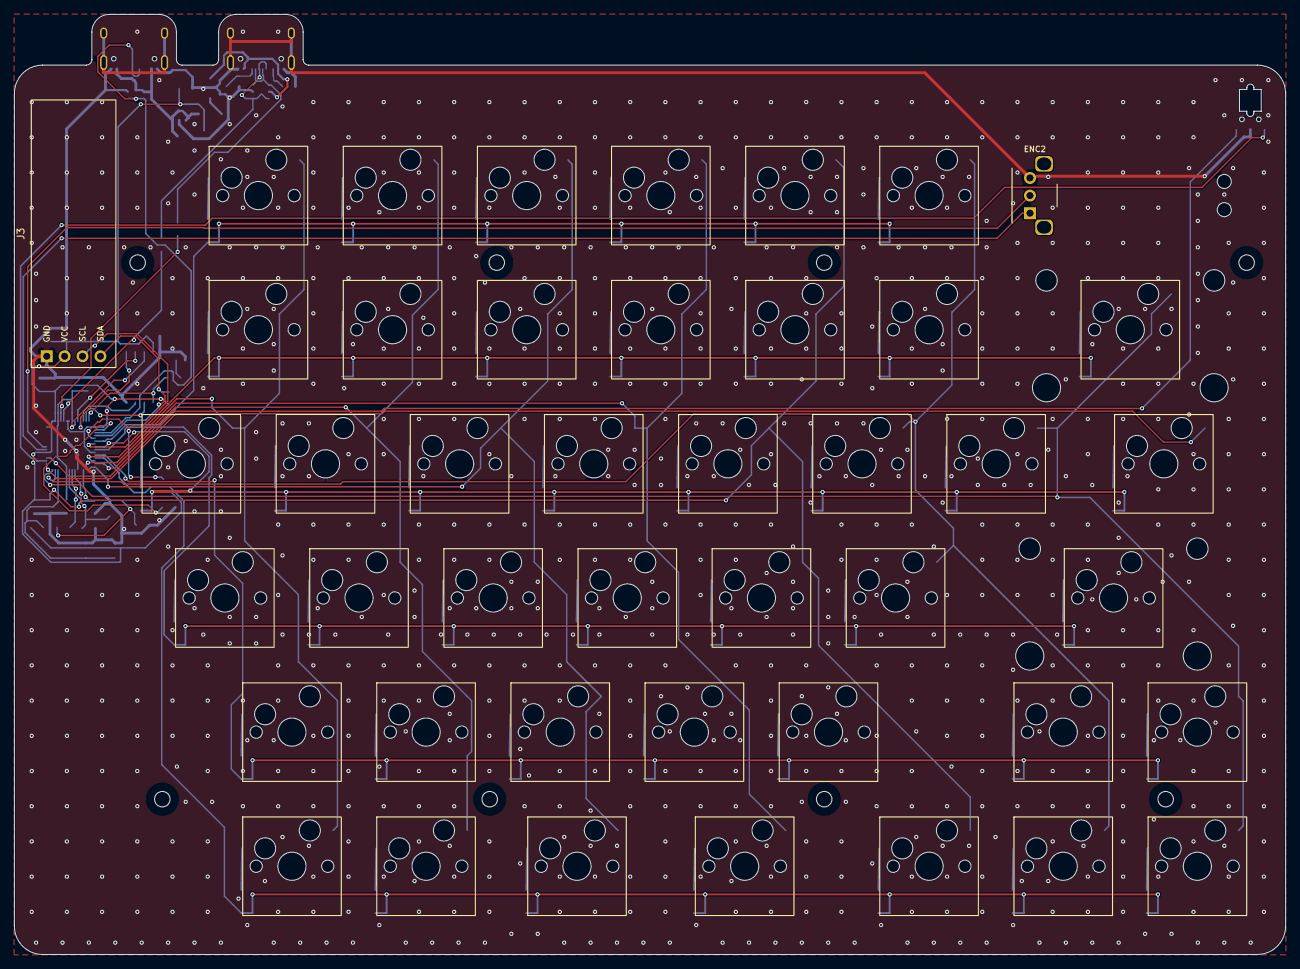
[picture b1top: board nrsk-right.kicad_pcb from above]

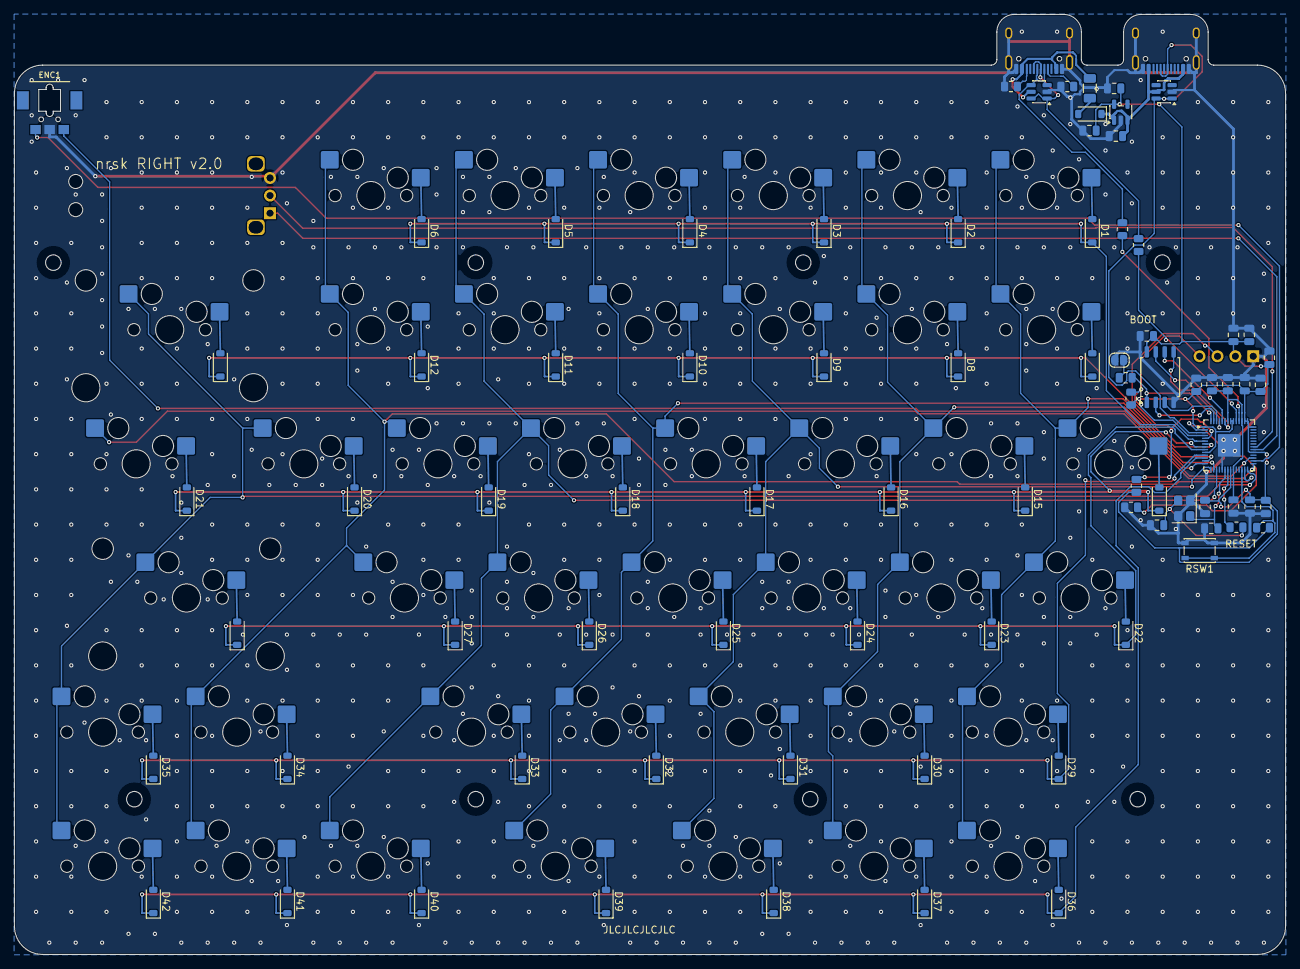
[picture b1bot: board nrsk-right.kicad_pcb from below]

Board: 2 copper layers, 180.5 x 133.5 mm, 136 parts (83 on the bottom side), 87 nets.

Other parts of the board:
DRUM1: Drum_Dial_Bearing
H1, H2, H3, H4, H5, H6, H7, H8: M2; MountingHole_2.2mm_M2

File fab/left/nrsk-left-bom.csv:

"Refs","Value","Footprint","Qty"
"C1,C2","15pF","Capacitor_SMD:C_0805_2012Metric","2"
"C3,C4,C16,C17","1uF","Capacitor_SMD:C_0805_2012Metric","4"
"C5,C6,C7,C8,C11,C12,C13,C14,C15,C18,C20","0.1uF","Capacitor_SMD:C_0805_2012Metric","11"
"C19","10uF","Capacitor_SMD:C_0805_2012Metric","1"
"D1,D2,D3,D4,D5,D6,D7,D8,D9,D10,D11,D12,D13,D14,D15,D16,D17,D18,D19,D20,D21,D22,D23,D24,D25,D26,D27,D28,D29,D30,D31,D32,D33,D34,D35,D36,D37,D38","1N4148W","Diode_SMD:D_SOD-123","38"
"D99","B5819W","Diode_SMD:D_SOD-123","1"
"ENC1","EC05E1220401","nrsk:Alps_EC05E1220401","1"
"F1","500mA","Fuse:Fuse_1206_3216Metric","1"
"J1,J2","USB-C","nrsk:USB_C_Receptacle_HRO_TYPE-C-31-M-12","2"
"J3","OLED 128x32","nrsk:OLED_0.91in_128x32_I2C","1"
"JP1","BOOTSEL","Jumper:SolderJumper-2_P1.3mm_Open_RoundedPad1.0x1.5mm","1"
"R1,R6","10k","Resistor_SMD:R_0805_2012Metric","2"
"R2,R3","27","Resistor_SMD:R_0805_2012Metric","2"
"R4,R5","5.1k","Resistor_SMD:R_0805_2012Metric","2"
"R7,R10","1k","Resistor_SMD:R_0805_2012Metric","2"
"R8,R9","4.7k","Resistor_SMD:R_0805_2012Metric","2"
"RSW1","Reset","Button_Switch_SMD:SW_SPST_PTS810","1"
"SW1","Esc","nrsk:SW_MX_Hotswap_1.00u","1"
"SW2","F1","nrsk:SW_MX_Hotswap_1.00u","1"
"SW3","F2","nrsk:SW_MX_Hotswap_1.00u","1"
"SW4","F3","nrsk:SW_MX_Hotswap_1.00u","1"
"SW5","F4","nrsk:SW_MX_Hotswap_1.00u","1"
"SW6","F5","nrsk:SW_MX_Hotswap_1.00u","1"
"SW7","F6","nrsk:SW_MX_Hotswap_1.00u","1"
"SW8","`","nrsk:SW_MX_Hotswap_1.00u","1"
"SW9","1","nrsk:SW_MX_Hotswap_1.00u","1"
"SW10","2","nrsk:SW_MX_Hotswap_1.00u","1"
"SW11","3","nrsk:SW_MX_Hotswap_1.00u","1"
"SW12","4","nrsk:SW_MX_Hotswap_1.00u","1"
"SW13","5","nrsk:SW_MX_Hotswap_1.00u","1"
"SW14","6","nrsk:SW_MX_Hotswap_1.00u","1"
"SW15","Tab","nrsk:SW_MX_Hotswap_1.50u","1"
"SW16","Q","nrsk:SW_MX_Hotswap_1.00u","1"
"SW17","W","nrsk:SW_MX_Hotswap_1.00u","1"
"SW18","E","nrsk:SW_MX_Hotswap_1.00u","1"
"SW19","R","nrsk:SW_MX_Hotswap_1.00u","1"
"SW20","T","nrsk:SW_MX_Hotswap_1.00u","1"
"SW21","Ctrl","nrsk:SW_MX_Hotswap_1.75u","1"
"SW22","A","nrsk:SW_MX_Hotswap_1.00u","1"
"SW23","S","nrsk:SW_MX_Hotswap_1.00u","1"
"SW24","D","nrsk:SW_MX_Hotswap_1.00u","1"
"SW25","F","nrsk:SW_MX_Hotswap_1.00u","1"
"SW26","G","nrsk:SW_MX_Hotswap_1.00u","1"
"SW27","Shift","nrsk:SW_MX_Hotswap_2.25u","1"
"SW28","Z","nrsk:SW_MX_Hotswap_1.00u","1"
"SW29","X","nrsk:SW_MX_Hotswap_1.00u","1"
"SW30","C","nrsk:SW_MX_Hotswap_1.00u","1"
"SW31","V","nrsk:SW_MX_Hotswap_1.00u","1"
"SW32","B","nrsk:SW_MX_Hotswap_1.00u","1"
"SW33","Ctrl","nrsk:SW_MX_Hotswap_1.25u","1"
"SW34","Opt","nrsk:SW_MX_Hotswap_1.25u","1"
"SW35","Cmd","nrsk:SW_MX_Hotswap_1.25u","1"
"SW36,SW37,SW38","Space","nrsk:SW_MX_Hotswap_1.00u","3"
"U1","RP2040","Package_DFN_QFN:QFN-56-1EP_7x7mm_P0.4mm_EP3.2x3.2mm","1"
"U2,U3","USBLC6-2SC6","Package_TO_SOT_SMD:SOT-23-6","2"
"U4","AP2112K-3.3","Package_TO_SOT_SMD:SOT-23-5","1"
"U5","W25Q128JVS","Package_SO:SOIC-8_5.3x5.3mm_P1.27mm","1"
"Y1","12MHz","Crystal:Crystal_SMD_3225-4Pin_3.2x2.5mm","1"

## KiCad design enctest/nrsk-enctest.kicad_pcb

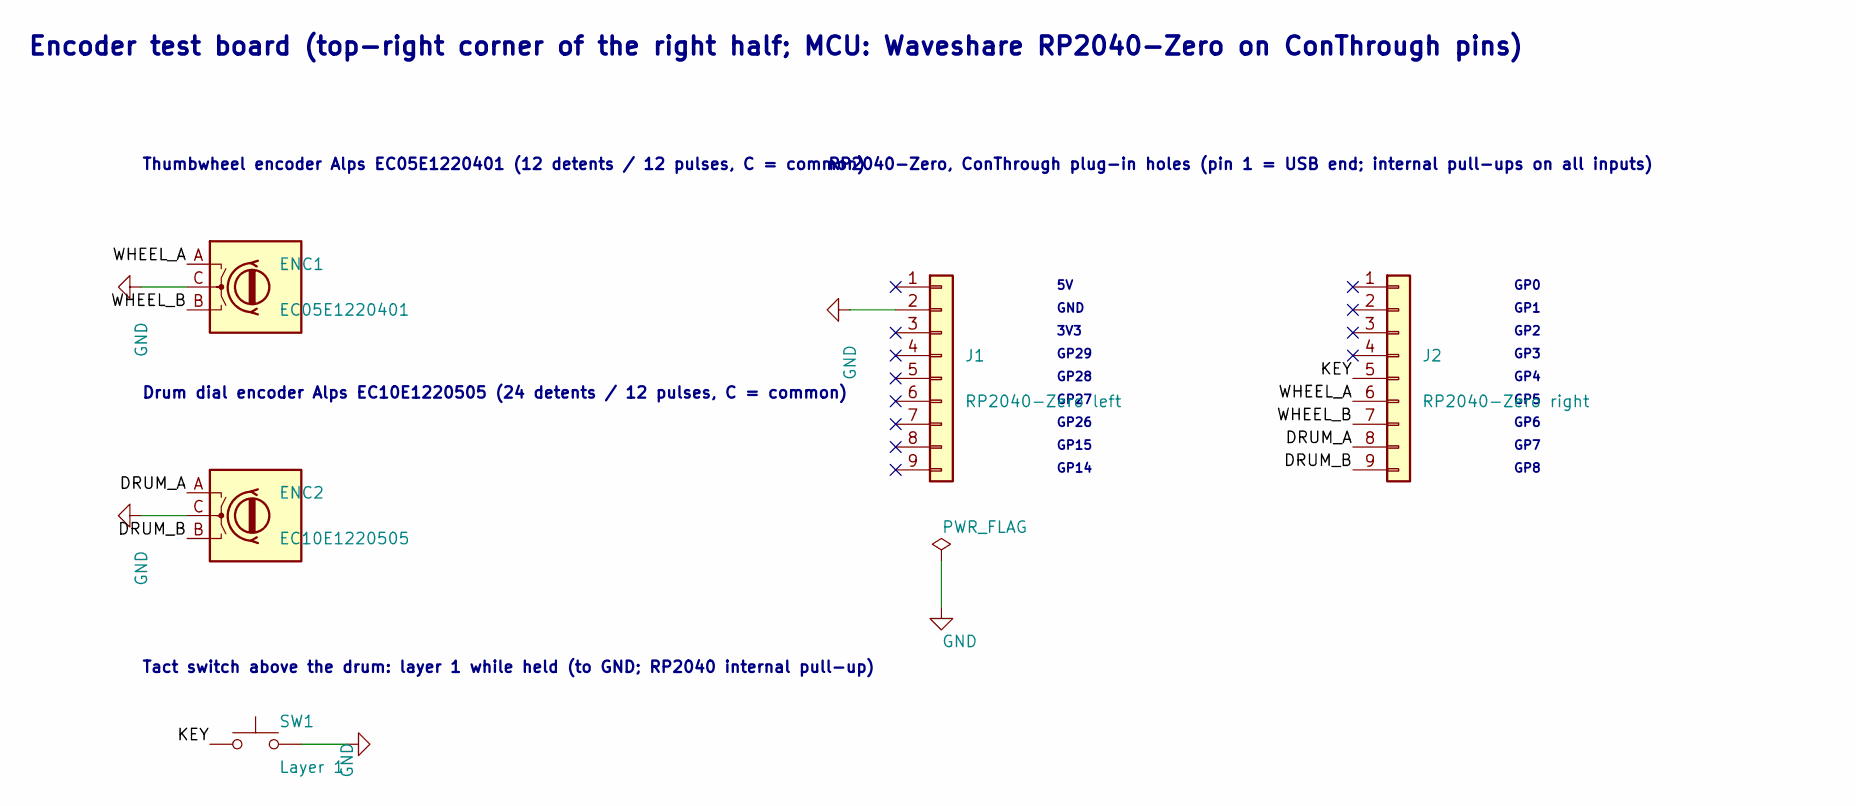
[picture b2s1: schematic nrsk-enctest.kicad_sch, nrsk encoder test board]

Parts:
ENC1: EC05E1220401; Alps_EC05E1220401
ENC2: EC10E1220505; Alps_EC10E
J1: RP2040-Zero left; ConThrough_1x09_P2.54mm_Contact
J2: RP2040-Zero right; ConThrough_1x09_P2.54mm_Contact
SW1: Layer 1; SW_PUSH_6mm_H9.5mm

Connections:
/DRUM_A: ENC2.A, J2.8
/DRUM_B: ENC2.B, J2.9
/KEY: J2.5, SW1.1
/WHEEL_A: ENC1.A, J2.6
/WHEEL_B: ENC1.B, J2.7
GND: ENC1.C, ENC2.C, J1.2, SW1.2

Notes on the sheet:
Encoder test board (top-right corner of the right half; MCU: Waveshare RP2040-Zero on ConThrough pins)
Thumbwheel encoder Alps EC05E1220401 (12 detents / 12 pulses, C = common)
Drum dial encoder Alps EC10E1220505 (24 detents / 12 pulses, C = common)
Tact switch above the drum: layer 1 while held (to GND; RP2040 internal pull-up)
RP2040-Zero, ConThrough plug-in holes (pin 1 = USB end; internal pull-ups on all inputs)
GND
3V3
GP29
GP28
GP27
GP26
GP15
GP14
GP0
GP1
GP2
GP3
GP4
GP5
GP6
GP7
GP8

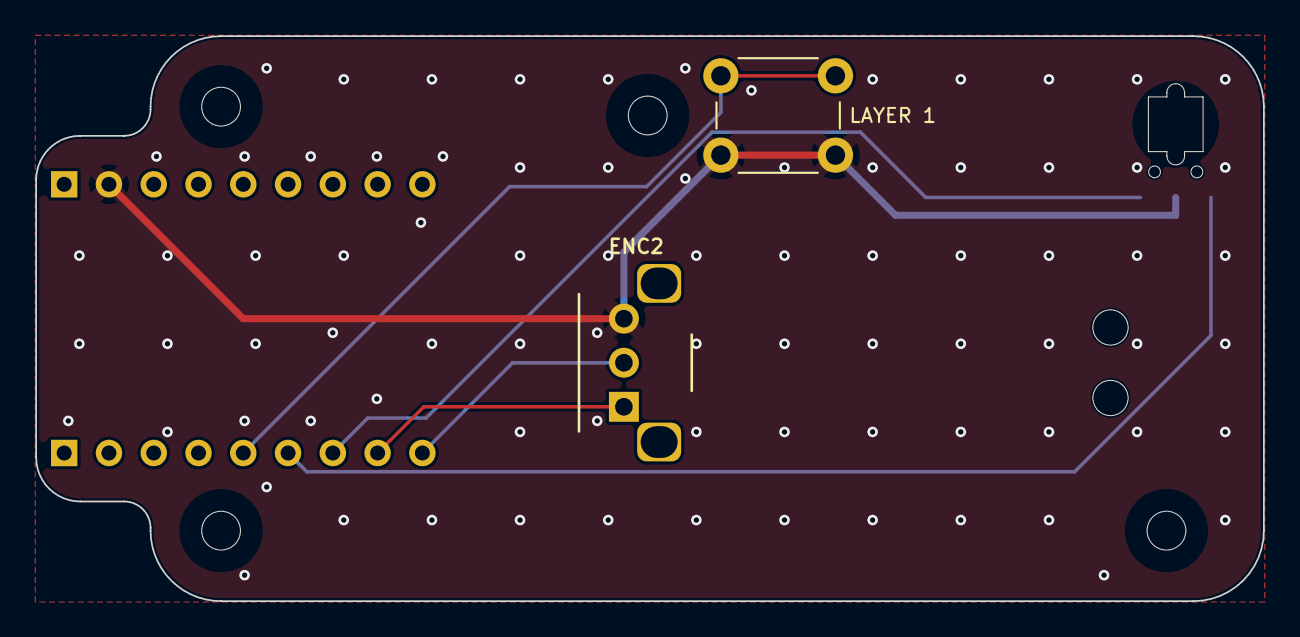
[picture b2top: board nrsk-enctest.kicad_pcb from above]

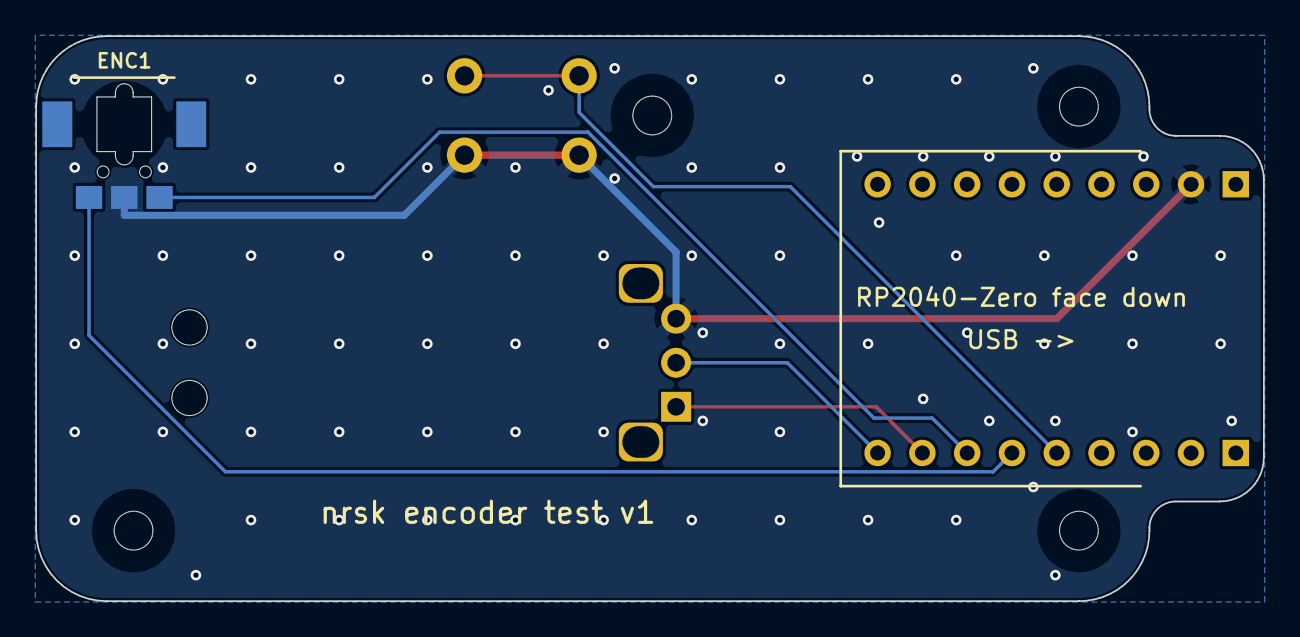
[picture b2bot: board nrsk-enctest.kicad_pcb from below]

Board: 2 copper layers, 69.6 x 32.0 mm, 10 parts (3 on the bottom side), 6 nets.

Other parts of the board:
DRUM1: Drum_Dial_Bearing
H1, H2, H3, H4: M2; MountingHole_2.2mm_M2

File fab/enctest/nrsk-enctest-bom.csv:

"Refs","Value","Footprint","Qty"
"ENC1","EC05E1220401","nrsk:Alps_EC05E1220401","1"
"ENC2","EC10E1220505","nrsk:Alps_EC10E","1"
"J1","RP2040-Zero left","nrsk:ConThrough_1x09_P2.54mm_Contact","1"
"J2","RP2040-Zero right","nrsk:ConThrough_1x09_P2.54mm_Contact","1"
"SW1","Layer 1","Button_Switch_THT:SW_PUSH_6mm_H9.5mm","1"

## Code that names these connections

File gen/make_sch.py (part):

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
import sexpr
import make_pro
from layout import (HERE, ROW_PINS, COL_PINS, SERIAL_PIN, HAND_PIN, I2C_SDA, I2C_SCL, WHEEL_PIN_A, WHEEL_PIN_B,
                    DRUM_PIN_A, DRUM_PIN_B, DRUM_SIDES,
                    N_ROWS, N_COLS, load)
from footprints import WIDTHS
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    'ldo': 'Package_TO_SOT_SMD:SOT-23-5',
    'boot': 'Jumper:SolderJumper-2_P1.3mm_Open_RoundedPad1.0x1.5mm',
    'esd': 'Package_TO_SOT_SMD:SOT-23-6',
    'xtal': 'Crystal:Crystal_SMD_3225-4Pin_3.2x2.5mm',   # reflowed by JLCPCB: the pads sit under the terminals
    'r': 'Resistor_SMD:R_0805_2012Metric',
    'c': 'Capacitor_SMD:C_0805_2012Metric',
    'fuse': 'Fuse:Fuse_1206_3216Metric',
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    # --- MCU ----------------------------------------------------------------
    MX, MY = 279.4, 116.84
    sh.text('MCU: RP2040 (QFN-56), 12 MHz, 3.3 V I/O, 16 MB QSPI flash', MX - 25.4, MY - 55.88)
    roles = {SERIAL_PIN: 'DATA', HAND_PIN: 'HAND', I2C_SDA: 'SDA', I2C_SCL: 'SCL', WHEEL_PIN_A: 'ENC_A', WHEEL_PIN_B: 'ENC_B'}
    if side in DRUM_SIDES:
        roles.update({DRUM_PIN_A: 'DRUM_A', DRUM_PIN_B: 'DRUM_B'})
    roles.update({p: f'ROW{i}' for i, p in enumerate(ROW_PINS)})
    used_cols = {k['col'] for k in keys}   # a column without keys on this half (COL7 on the left) stays unconnected
    roles.update({p: f'COL{i}' for i, p in enumerate(COL_PINS) if i in used_cols})
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    # crystal (Raspberry Pi reference: 1k in series with XOUT, 15 pF loads)
    sh.text('Clock', 190.5, 63.5)
    sh.symbol('Device:Crystal_GND24', 'Y1', '12MHz', 203.2, 76.2, 0, FP['xtal'], {'1': 'XIN', '3': 'XTAL', '2': 'GND', '4': 'GND'})
    two_pin(sh, 'Device:C', 'C1', '15pF', 190.5, 88.9, FP['c'], 'XIN', 'GND')
    two_pin(sh, 'Device:C', 'C2', '15pF', 215.9, 88.9, FP['c'], 'XTAL', 'GND')
    sh.symbol('Device:R', 'R10', '1k', 228.6, 76.2, 90, FP['r'], {'1': 'XTAL', '2': 'XOUT'})

    # decoupling
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
    # reset / bootloader
    sh.text('Reset (double-tap = bootloader) / BOOTSEL pads', 190.5, 160.02)
    two_pin(sh, 'Device:R', 'R6', '10k', 190.5, 175.26, FP['r'], '3V3', 'RUN')
    sh.symbol('Switch:SW_Push', 'RSW1', 'Reset', 205.74, 187.96, 0, FP['reset'], {'1': 'RUN', '2': 'GND'})
    two_pin(sh, 'Device:R', 'R7', '1k', 223.52, 175.26, FP['r'], 'QSPI_SS', 'BOOT')
    sh.symbol('Jumper:SolderJumper_2_Open', 'JP1', 'BOOTSEL', 236.22, 187.96, 0, FP['boot'], {'1': 'BOOT', '2': 'GND'})
    two_pin(sh, 'Device:R', 'R1', '10k', 251.46, 175.26, FP['r'], 'HAND', '3V3' if side == 'left' else 'GND')
    sh.text(f'Handedness: {HAND_PIN} {"high = left" if side == "left" else "low = right"}', 246.38, 190.5, 1.27)

    # 3.3 V regulator
    sh.text('3.3 V LDO', 190.5, 205.74)
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

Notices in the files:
README.md:
- MX スイッチ、Kailh ホットスワップソケット、スタビライザー：[kiswitch](https://github.com/kiswitch/kiswitch)（CC-BY-SA 4.0、設計データへの利用は例外規定あり）
